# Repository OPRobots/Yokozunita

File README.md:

# Yokozunita
Robot minisumo con PCBs, motores fingertech, plomo fundido y stepUp.

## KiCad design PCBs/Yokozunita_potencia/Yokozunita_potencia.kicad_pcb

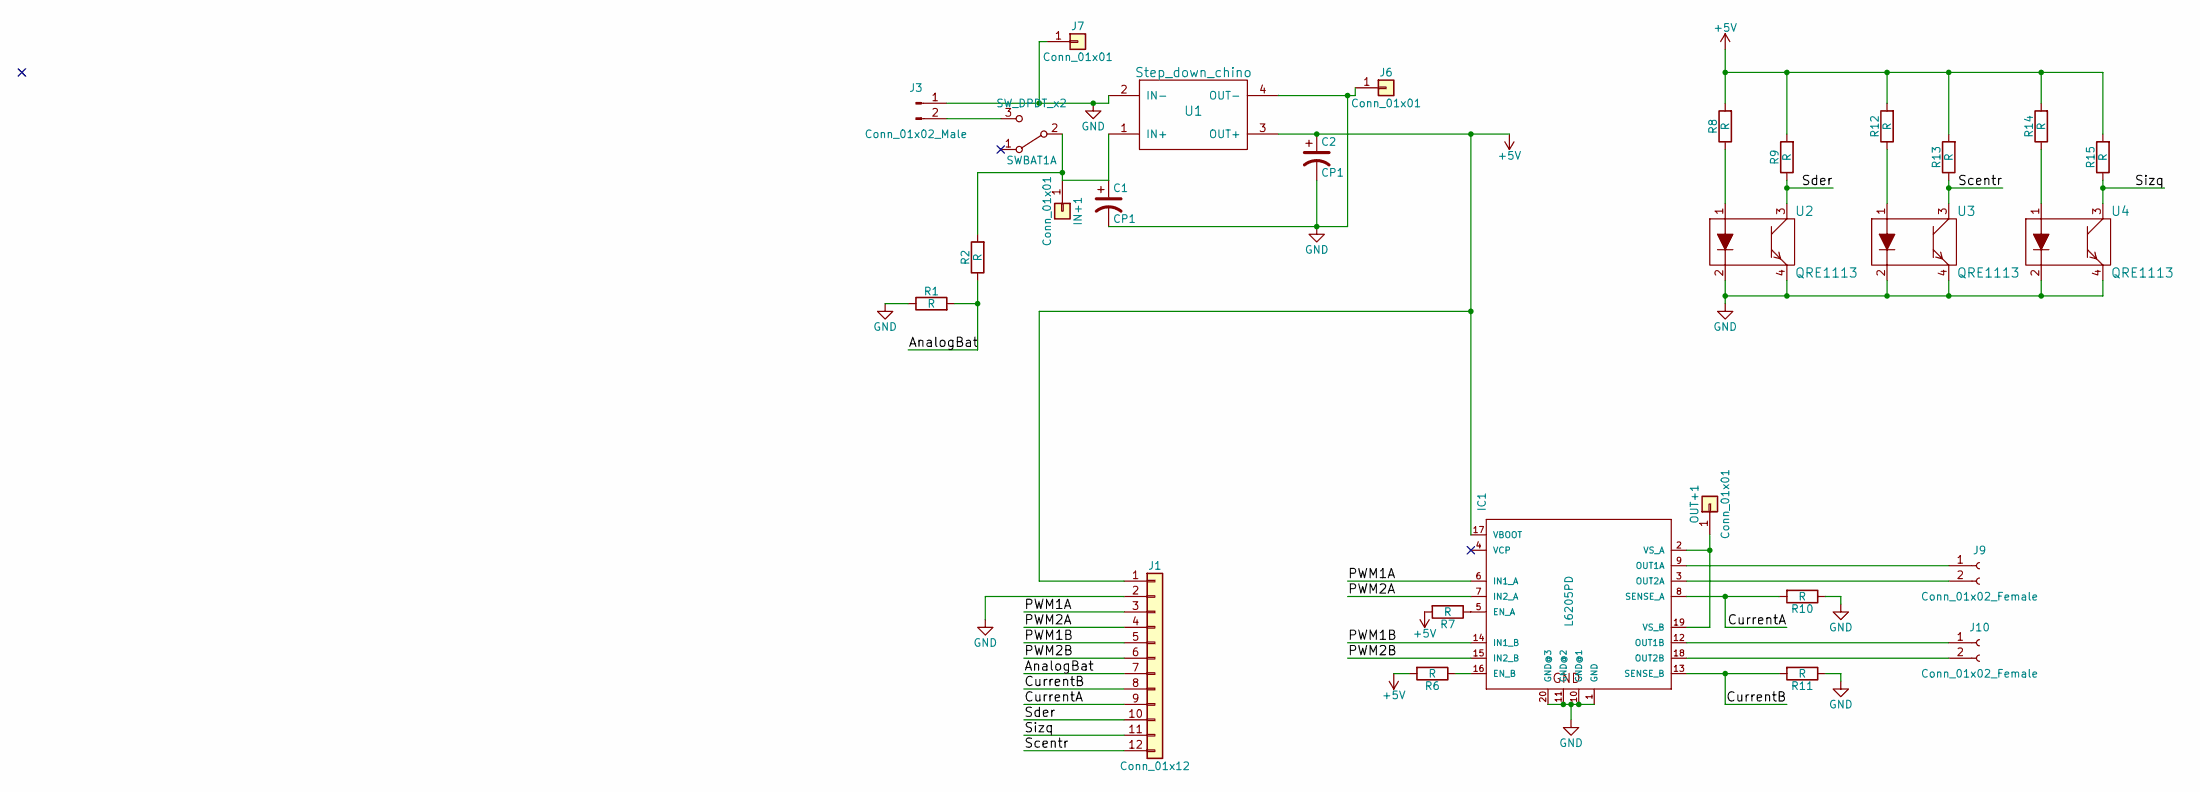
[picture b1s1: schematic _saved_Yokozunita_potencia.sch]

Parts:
C1: CP1; CP_Radial_D10.0mm_P7.50mm
C2: CP1; CP_Radial_D8.0mm_P5.00mm
IC1: L6205PD; POWERSO20
IN+1: Conn_01x01; Socket_Strip_Straight_1x01_Pitch2.54mm
J1: Conn_01x12; Hirose_FH12-12S-0.5SH_1x12-1MP_P0.50mm_Horizontal
J3: Conn_01x02_Male; Pin_Header_Straight_1x02_Pitch2.54mm
J6, J7: Conn_01x01; Socket_Strip_Straight_1x01_Pitch2.54mm
J9, J10: Conn_01x02_Female; Socket_Strip_Straight_1x02_Pitch2.54mm
OUT+1: Conn_01x01; Socket_Strip_Straight_1x01_Pitch2.54mm
R1, R2, R6, R7, R8, R9, R10, R11, R12, R13, R14, R15: R; R_0805
SWBAT1: SW_DPDT_x2; Socket_Strip_Straight_1x03_Pitch2.54mm
U1: Step_down_chino
U2, U3, U4: QRE1113

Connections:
+5V: C2.1, IC1.17 (VBOOT), J1.1, R6.2, R7.2, R8.2, R9.2, R12.2, R13.2, R14.2, R15.2, U1.3 (OUT+)
/AnalogBat: J1.7, R1.2, R2.1
/CurrentA: IC1.8 (SENSE_A), J1.9, R10.2; also elsewhere on the board
/CurrentB: IC1.13 (SENSE_B), J1.8, R11.2
/PWM1A: IC1.6 (IN1_A), J1.3
/PWM1B: IC1.14 (IN1_B), J1.5
/PWM2A: IC1.7 (IN2_A), J1.4
/PWM2B: IC1.15 (IN2_B), J1.6
/Scentr: J1.12, R13.1, U3.3
/Sder: J1.10, R9.1, U2.3
/Sizq: J1.11, R15.1, U4.3
GND: C1.2, C2.2, IC1.1 (GND), IC1.10 (GND@1), IC1.11 (GND@2), IC1.20 (GND@3), J1.2, J3.1, J6.1, J7.1, R1.1, R10.1, R11.1, U1.2 (IN-), U1.4 (OUT-), U2.2, U2.4, U3.2, U3.4, U4.2, U4.4; also elsewhere on the board
unnamed: C1.1, IN+1.1, R2.2, SWBAT1.2 (B), U1.1 (IN+)
unnamed: IC1.3 (OUT2A), J9.2
unnamed: IC1.5 (EN_A), R7.1
unnamed: IC1.9 (OUT1A), J9.1
unnamed: IC1.12 (OUT1B), J10.1
unnamed: IC1.16 (EN_B), R6.1
unnamed: IC1.18 (OUT2B), J10.2
unnamed: IC1.2 (VS_A), IC1.19 (VS_B), OUT+1.1
unnamed: J3.2, SWBAT1.3 (C)
unnamed: R8.1, U2.1
unnamed: R12.1, U3.1
unnamed: R14.1, U4.1

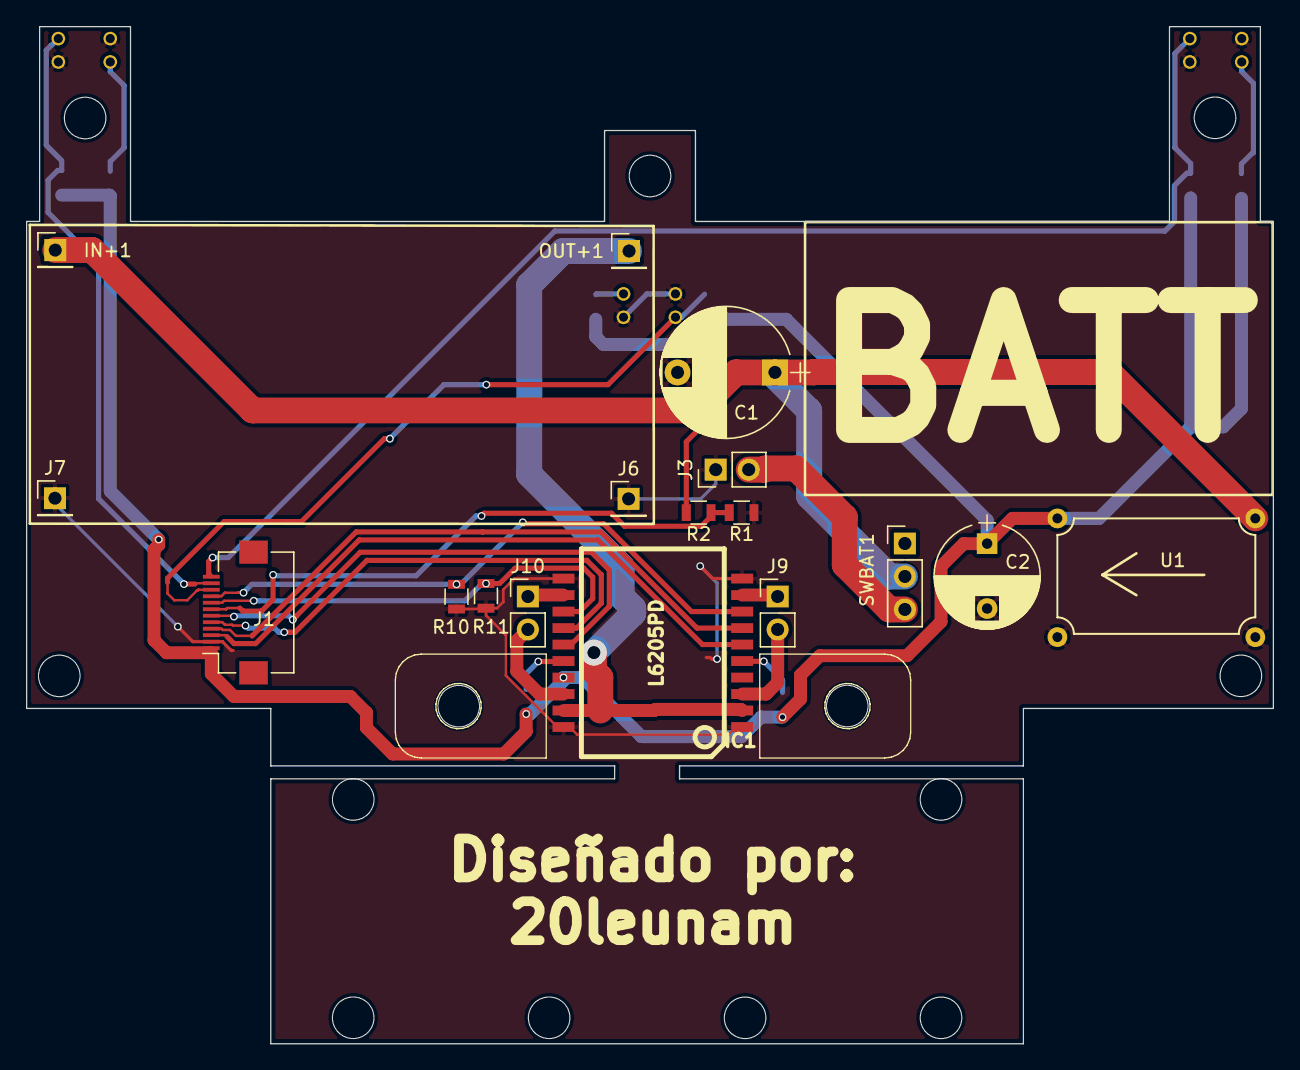
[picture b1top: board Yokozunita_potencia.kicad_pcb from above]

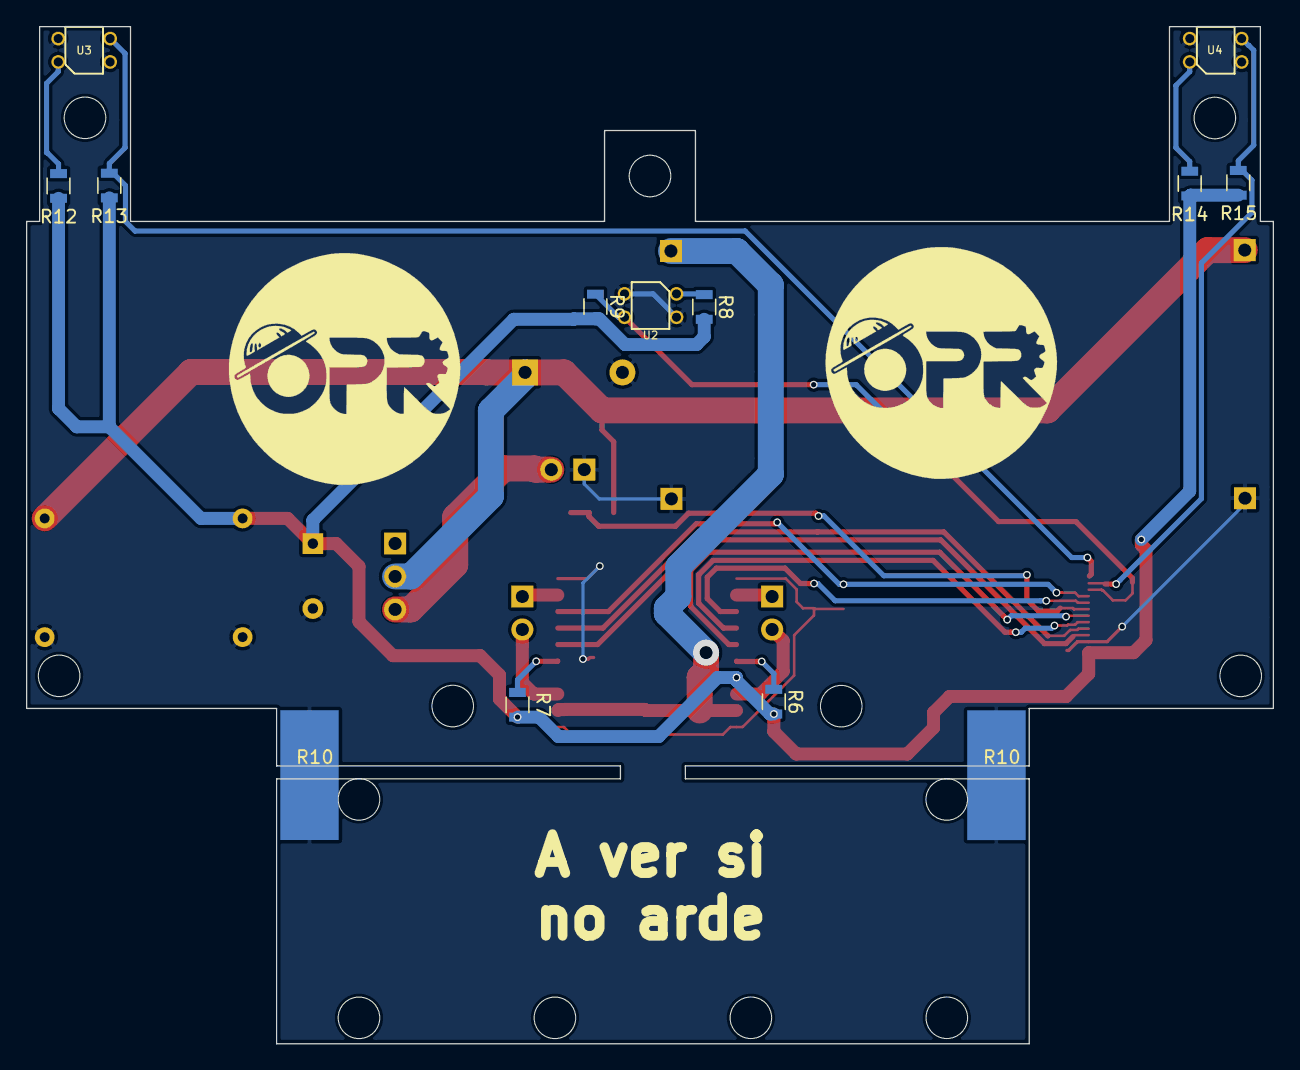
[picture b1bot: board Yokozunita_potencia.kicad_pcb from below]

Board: 2 copper layers, 96.0 x 78.3 mm, 30 parts (13 on the bottom side), 24 nets.

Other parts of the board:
R10#2, R10#3: R; R_0805

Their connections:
/CurrentA: R10#3.2; also elsewhere on the board
GND: R10#2.1, R10#3.1; also elsewhere on the board

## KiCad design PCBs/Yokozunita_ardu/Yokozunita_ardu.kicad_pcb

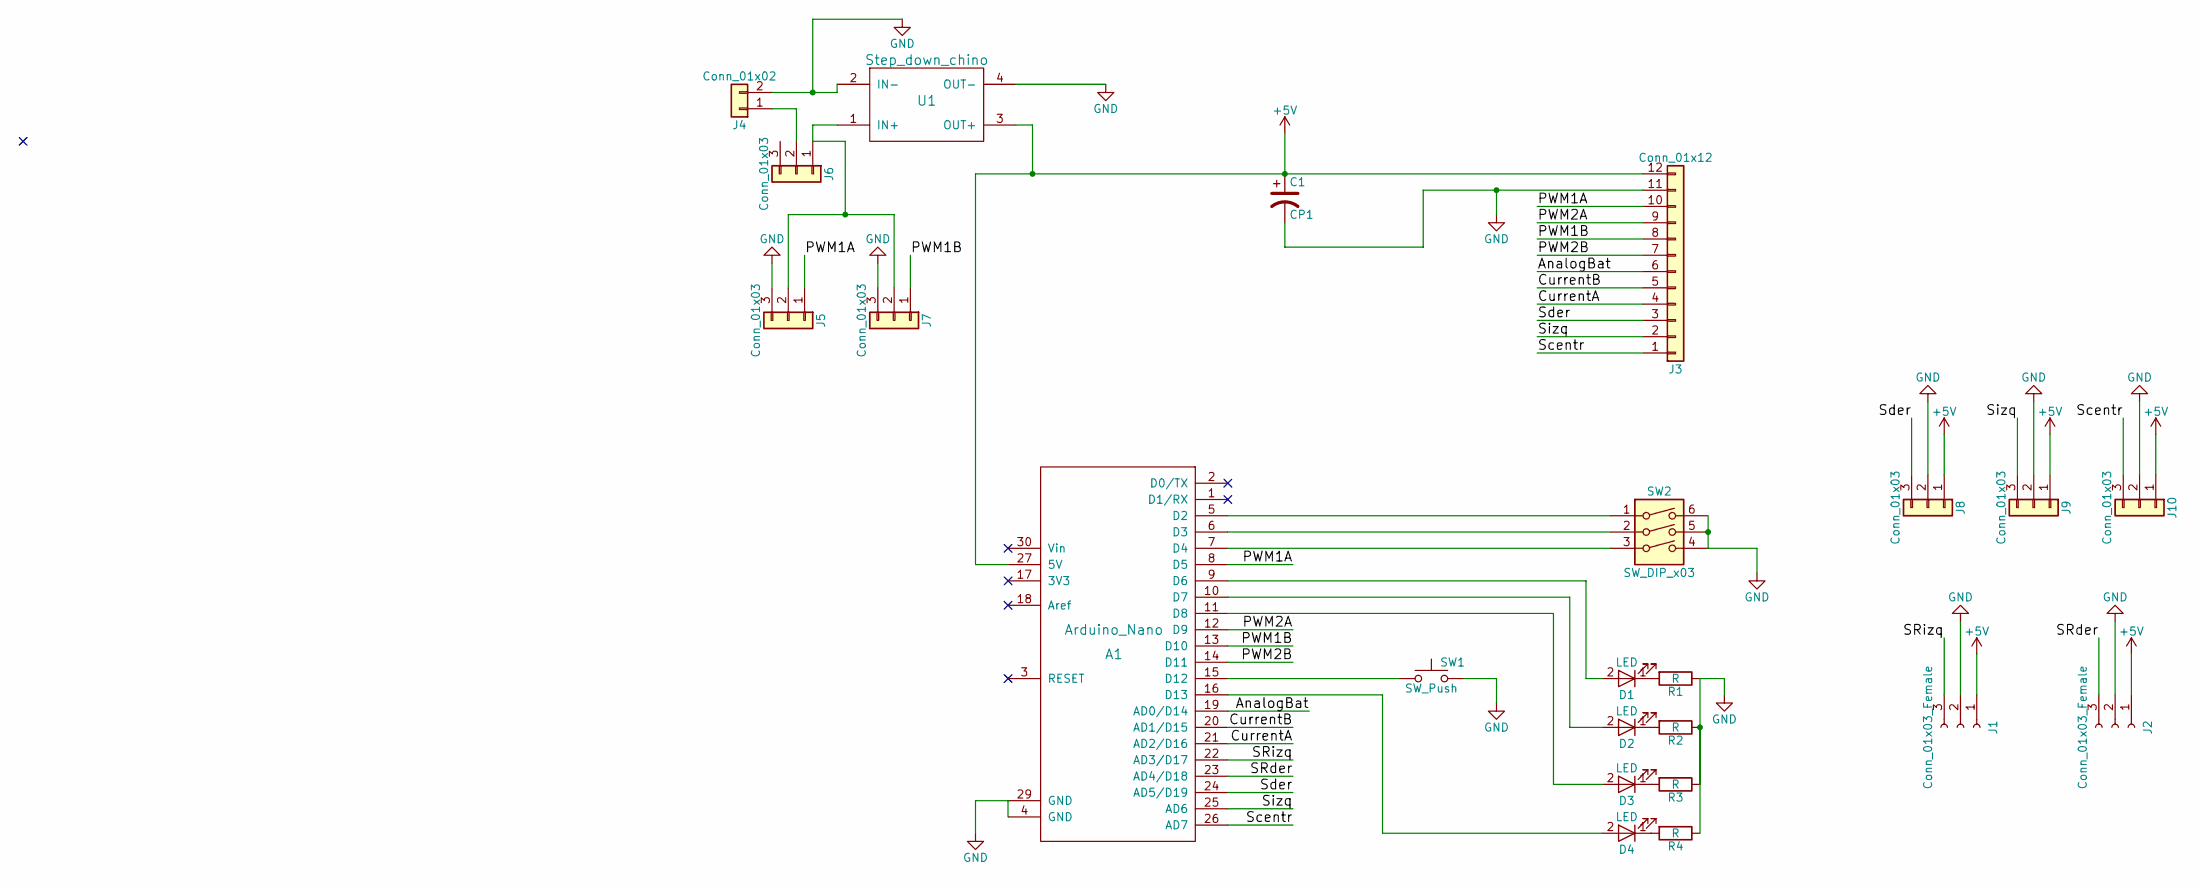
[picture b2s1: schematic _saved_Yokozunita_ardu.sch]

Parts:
A1: Arduino_Nano; arduino_nano
C1: CP1; CP_Radial_D8.0mm_P3.80mm
D1, D2, D3, D4: LED; LED_D3.0mm
J1, J2: Conn_01x03_Female; Pin_Header_Straight_1x03_Pitch2.54mm
J3: Conn_01x12; Hirose_FH12-12S-0.5SH_1x12-1MP_P0.50mm_Horizontal
J4: Conn_01x02; Pin_Header_Straight_1x02_Pitch2.54mm
J5, J6, J7, J8, J9, J10: Conn_01x03; Pin_Header_Straight_1x03_Pitch2.54mm
R1, R2, R3, R4: R; R_0805
SW1: SW_Push; SW_DIP_x1_W8.61mm_Slide_LowProfile
SW2: SW_DIP_x03; SW_DIP_x3_W8.61mm_Slide_LowProfile
U1: Step_down_chino

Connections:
+5V: A1.27 (5V), C1.1, J1.1, J2.1, J3.12, J8.1, J9.1, J10.1, U1.3 (OUT+)
/AnalogBat: A1.19 (AD0/D14), J3.6
/CurrentA: A1.21 (AD2/D16), J3.4
/CurrentB: A1.20 (AD1/D15), J3.5
/PWM1A: A1.8 (D5), J3.10, J5.1
/PWM1B: A1.13 (D10), J3.8, J7.1
/PWM2A: A1.12 (D9), J3.9
/PWM2B: A1.14 (D11), J3.7
/SRder: A1.23 (AD4/D18), J2.3
/SRizq: A1.22 (AD3/D17), J1.3
/Scentr: A1.26 (AD7), J3.1, J10.3
/Sder: A1.24 (AD5/D19), J3.3, J8.3
/Sizq: A1.25 (AD6), J3.2, J9.3
GND: A1.4 (GND), A1.29 (GND), C1.2, J1.2, J2.2, J3.11, J4.2, J5.3, J7.3, J8.2, J9.2, J10.2, R1.1, R2.1, R3.1, R4.1, SW1.2, SW2.4, SW2.5, SW2.6, U1.2 (IN-), U1.4 (OUT-)
unnamed: A1.5 (D2), SW2.1
unnamed: A1.6 (D3), SW2.2
unnamed: A1.7 (D4), SW2.3
unnamed: A1.9 (D6), D1.2 (A)
unnamed: A1.10 (D7), D2.2 (A)
unnamed: A1.11 (D8), D3.2 (A)
unnamed: A1.15 (D12), SW1.1
unnamed: A1.16 (D13), D4.2 (A)
unnamed: D1.1 (K), R1.2
unnamed: D2.1 (K), R2.2
unnamed: D3.1 (K), R3.2
unnamed: D4.1 (K), R4.2
unnamed: J4.1, J6.2
unnamed: J5.2, J6.1, J7.2, U1.1 (IN+)

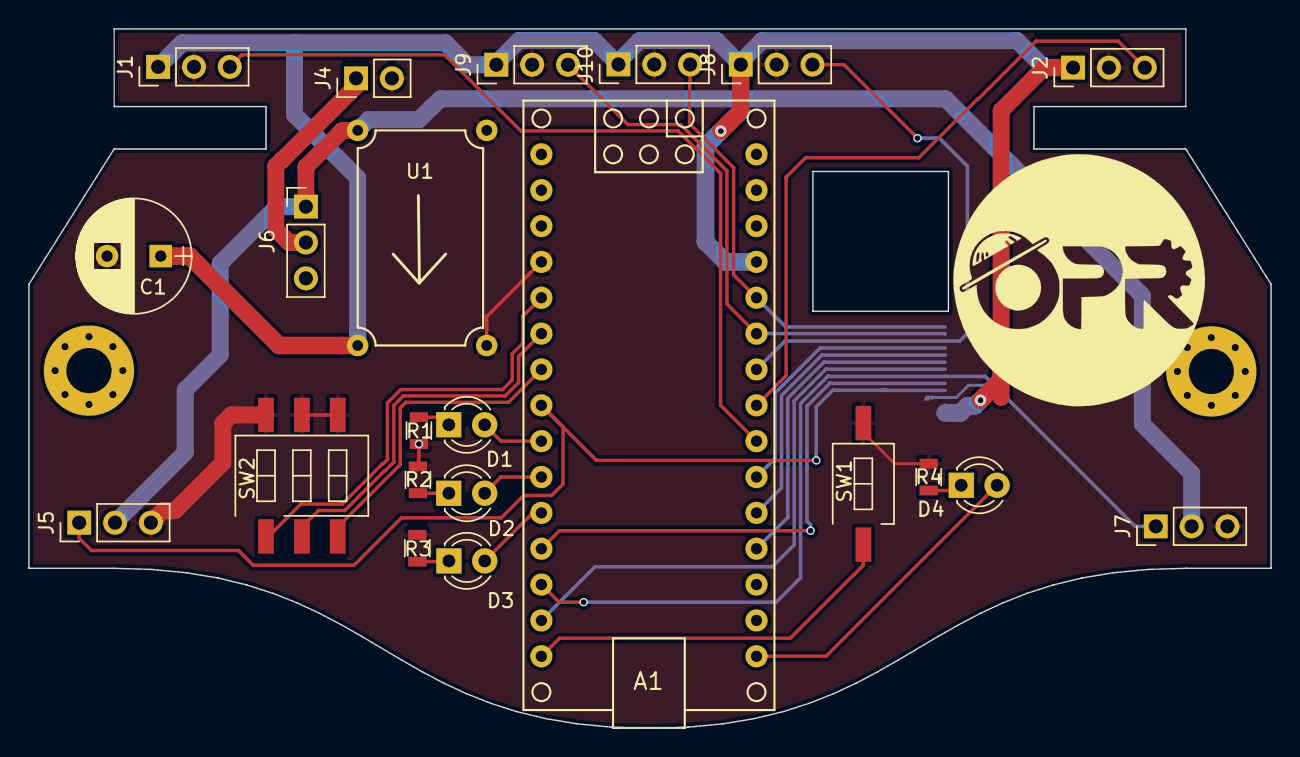
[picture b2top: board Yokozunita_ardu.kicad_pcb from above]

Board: 2 copper layers, 88.0 x 49.5 mm, 23 parts (1 on the bottom side), 28 nets.
